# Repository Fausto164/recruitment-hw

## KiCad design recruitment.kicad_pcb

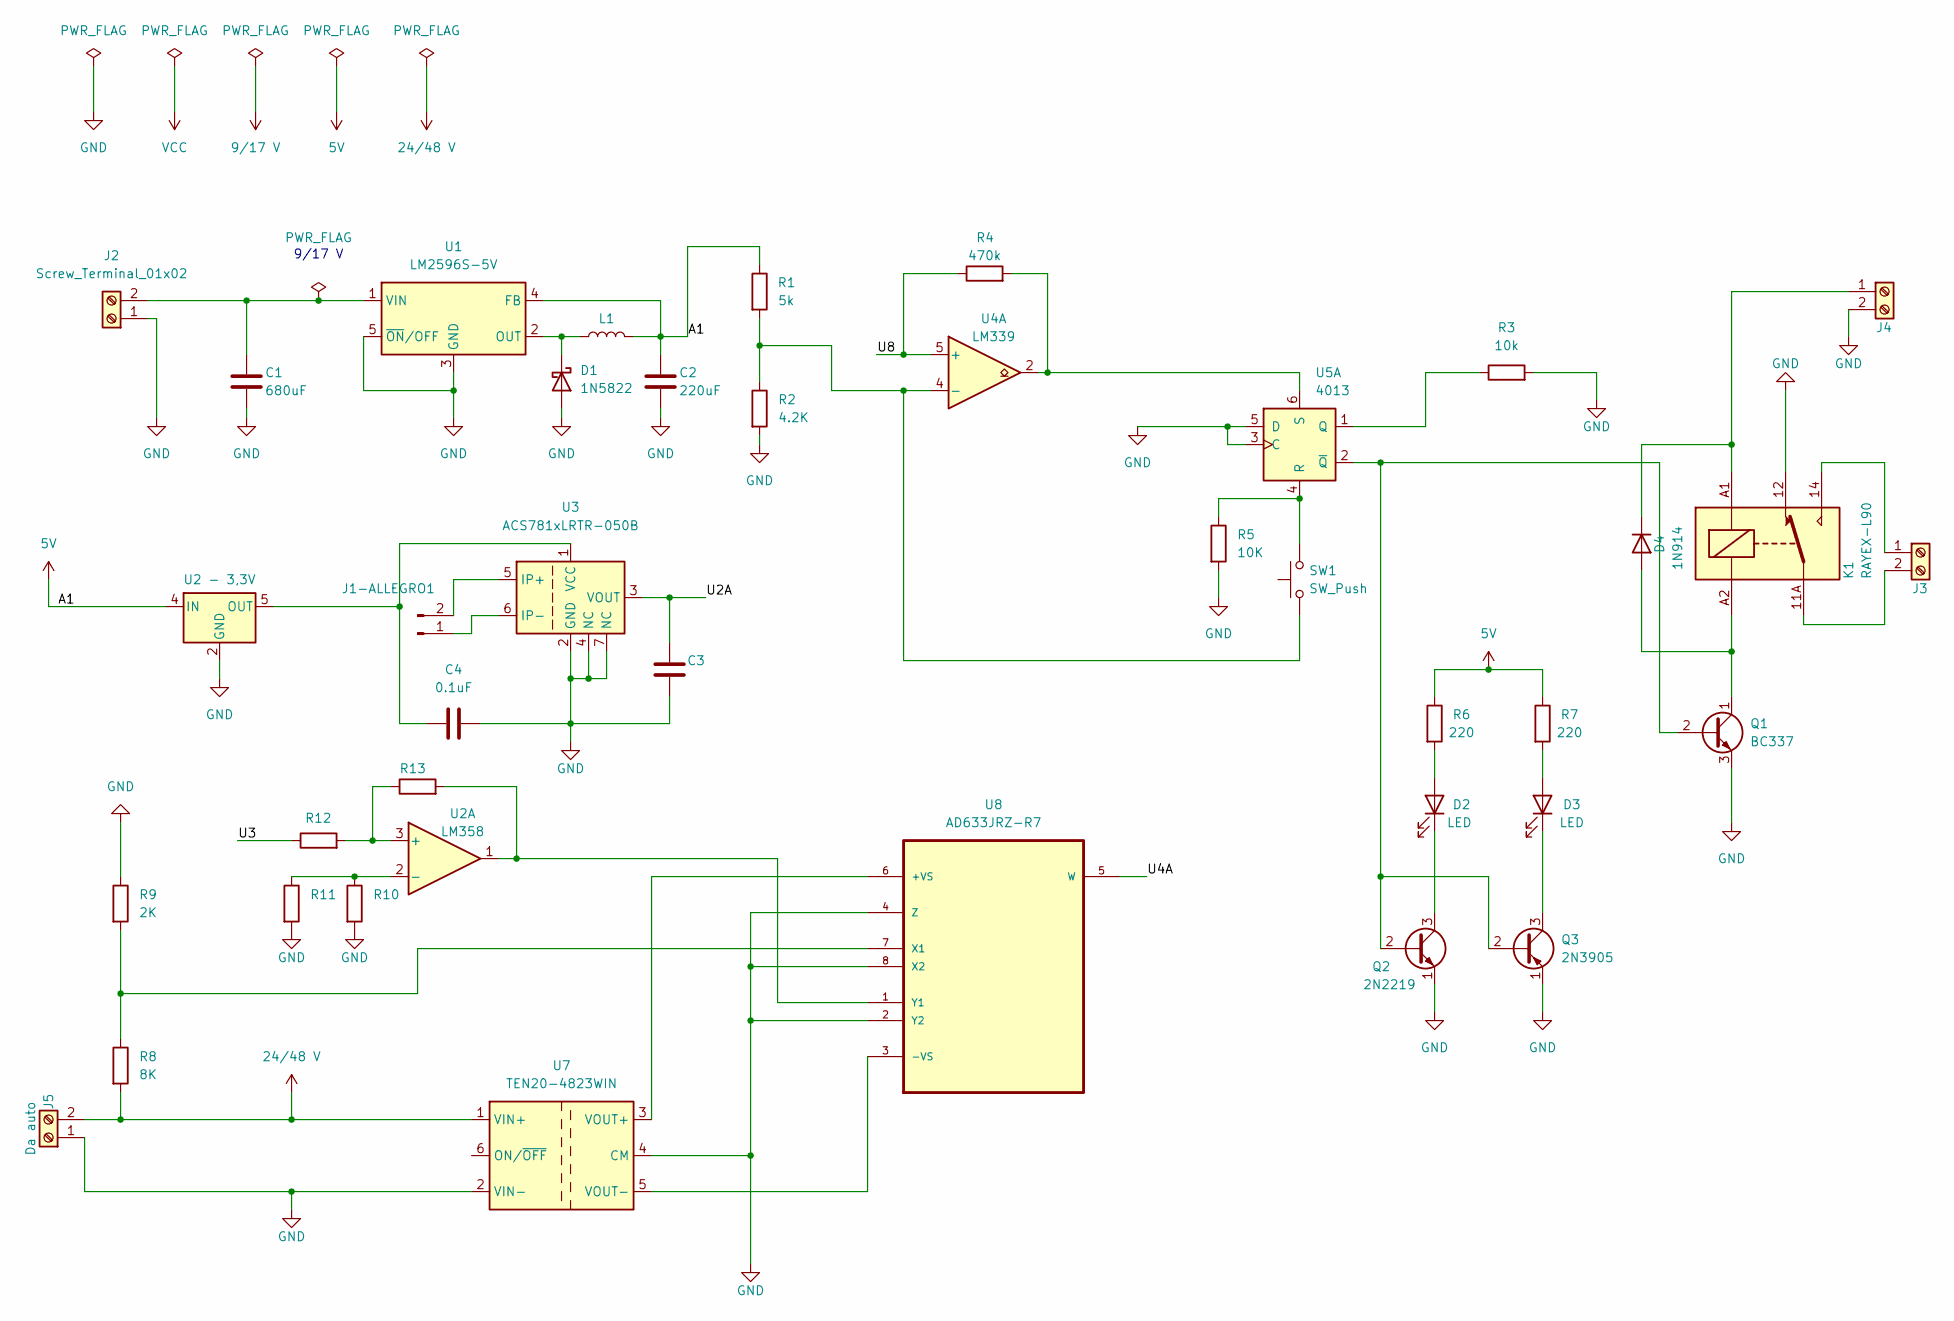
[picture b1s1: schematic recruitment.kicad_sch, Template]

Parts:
C1: 680uF; C_0402_1005Metric
C2: 220uF; C_0402_1005Metric
C3: C_0402_1005Metric
C4: 0.1uF; C_0402_1005Metric
D1: 1N5822; D_DO-201AD_P15.24mm_Horizontal
D2, D3: LED; LED_0201_0603Metric_Pad0.64x0.40mm_HandSolder
D4: 1N914; D_DO-35_SOD27_P7.62mm_Horizontal
J1-ALLEGRO1: Conn_01x02_Pin; PhoenixContact_GMSTBA_2,5_2-G_1x02_P7.50mm_Horizontal
J2, J3, J4: Screw_Terminal_01x02; PhoenixContact_GMSTBA_2,5_2-G_1x02_P7.50mm_Horizontal
J5: Da auto; PhoenixContact_GMSTBA_2,5_2-G_1x02_P7.50mm_Horizontal
K1: RAYEX-L90; Relay_SPDT_RAYEX-L90
L1: L; L_0805_2012Metric
Q1: BC337; TO-92_Inline
Q2: 2N2219; TO-92L_Inline
Q3: 2N3905; TO-92_Inline
R1: 470k; R_0201_0603Metric
R2: 5k; R_0201_0603Metric
R3, R11, R13: 10k; R_0201_0603Metric
R4: 4.2K; R_0201_0603Metric
R5, R10, R12: 10K; R_0201_0603Metric
R6, R7: 220; R_0201_0603Metric
R8: 8K; R_0201_0603Metric
R9: 2K; R_0201_0603Metric
SW1: SW_Push; SW_SPST_TS-1088-xR020
U1: LM2596S-5V; TO-263-5_TabPin3
U2: LM358; SOIC-8-1EP_3.9x4.9mm_P1.27mm_EP2.29x3mm
U2-TPS71533__SC70: U2 - 3,3V; SOT-353_SC-70-5
U3: ACS781xLRTR-050B; Allegro_PSOF-7_4.8x6.4mm_P1.60mm
U4: LM339; SOT-23-6
U5: 4013; DIP-14_W7.62mm
U7: TEN20-4823WIN; Converter_DCDC_TRACO_TEN20-xxxx_THT
U8: AD633JRZ-R7; SOIC-8-1EP_3.9x4.9mm_P1.27mm_EP2.29x3mm; MPN AD633JRZ-R7

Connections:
5V: C2.1, L1.2, R2.1, R6.1, R7.1, U1.4 (FB), U2-TPS71533__SC70.4 (IN)
24/48 V: J5.2, R8.2, U7.1 (VIN+)
/U2A: C3.1, U3.3 (VOUT)
/U3: R12.1
/U4A: U8.5 (W)
/U8: R1.1, U4.5 (+)
GND: C1.2, C2.2, C3.2, C4.1, D1.2 (A), J2.1, J4.2, J5.1, K1.12, Q1.3 (E), Q2.1 (E), Q3.1 (E), R3.2, R4.2, R5.2, R9.1, R10.2, R11.2, U1.3 (GND), U1.5 (~ON/OFF), U2-TPS71533__SC70.2 (GND), U3.2 (GND), U3.4 (NC), U3.7 (NC), U5.3 (C), U5.5 (D), U7.2 (VIN-), U7.4 (CM), U8.2 (Y2), U8.4 (Z), U8.8 (X2)
unnamed: D1.1 (K), L1.1, U1.2 (OUT)
unnamed: D2.2 (A), R6.2
unnamed: D2.1 (K), Q2.3 (C)
unnamed: D3.2 (A), R7.2
unnamed: D3.1 (K), Q3.3 (C)
unnamed: D4.2 (A), K1.A2, Q1.1 (C)
unnamed: D4.1 (K), J4.1, K1.A1
unnamed: J1-ALLEGRO1.1, U3.6 (IP-)
unnamed: J1-ALLEGRO1.2, U3.5 (IP+)
unnamed: C1.1, J2.2, U1.1 (VIN)
unnamed: J3.1, K1.14
unnamed: J3.2, K1.11A, K1.11B
unnamed: Q1.2 (B), Q2.2 (B), Q3.2 (B), U5.2 (~Q)
unnamed: C4.2, U2-TPS71533__SC70.5 (OUT), U3.1 (VCC)
unnamed: R12.2, R13.1, U2.3 (+)
unnamed: R10.1, R11.1, U2.2 (-)
unnamed: R2.2, R4.1, SW1.1, U4.4 (-)
unnamed: R3.1, U5.1 (Q)
unnamed: R5.1, SW1.2, U5.4 (R)
unnamed: R1.2, U4.2, U5.6 (S)
unnamed: U7.3 (VOUT+), U8.6 (+VS)
unnamed: U7.5 (VOUT-), U8.3 (-VS)
unnamed: R8.1, R9.2, U8.7 (X1)
unnamed: R13.2, U2.1, U8.1 (Y1)

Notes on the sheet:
9/17 V

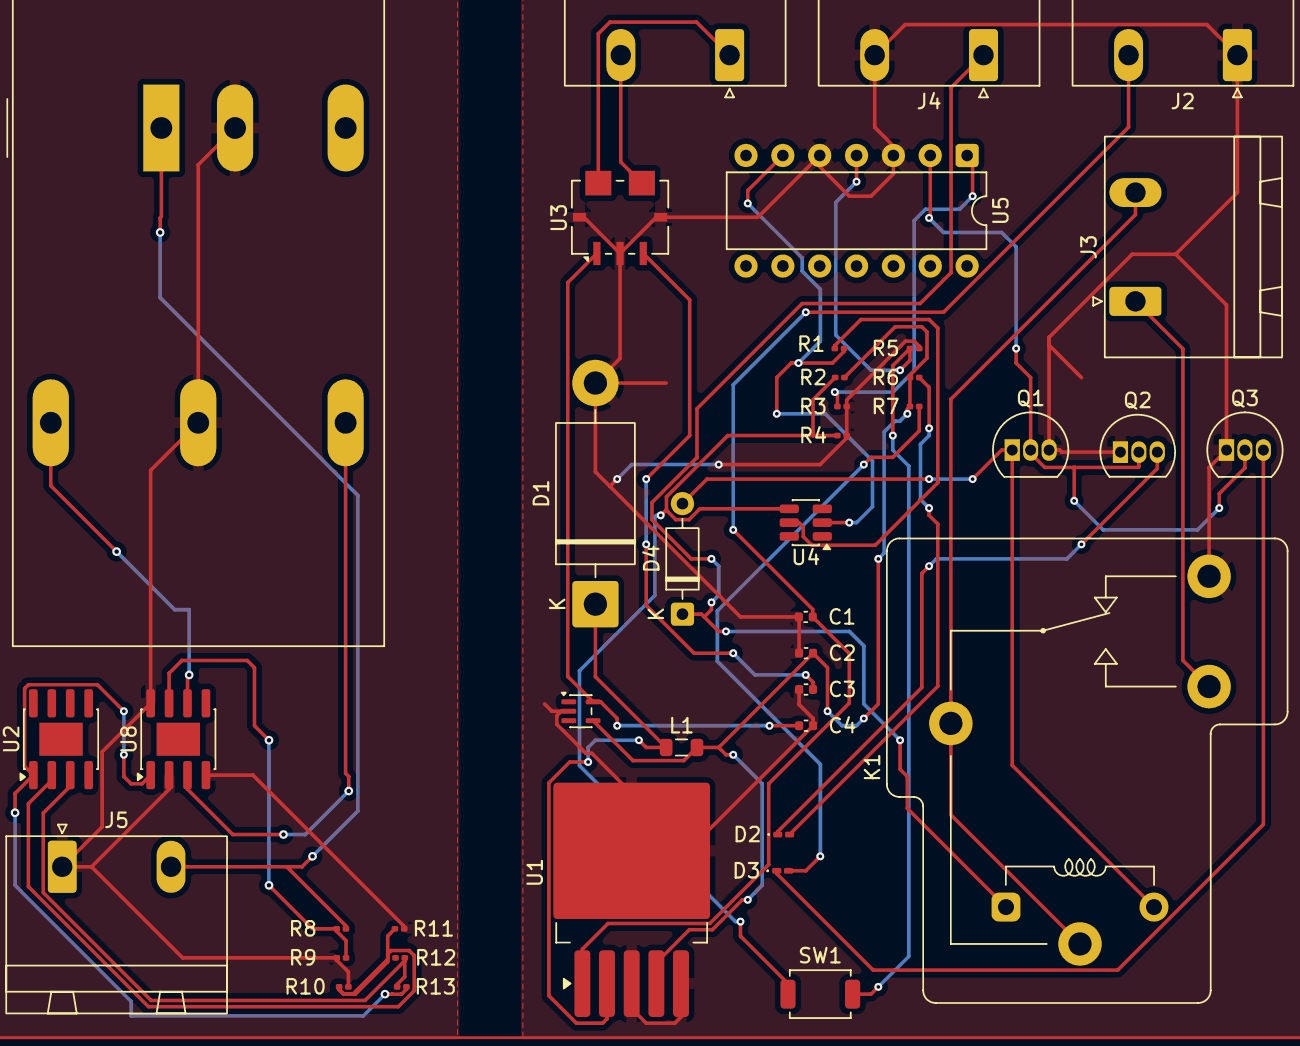
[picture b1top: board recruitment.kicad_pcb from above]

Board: 2 copper layers, 40 parts (0 on the bottom side), 29 nets.
